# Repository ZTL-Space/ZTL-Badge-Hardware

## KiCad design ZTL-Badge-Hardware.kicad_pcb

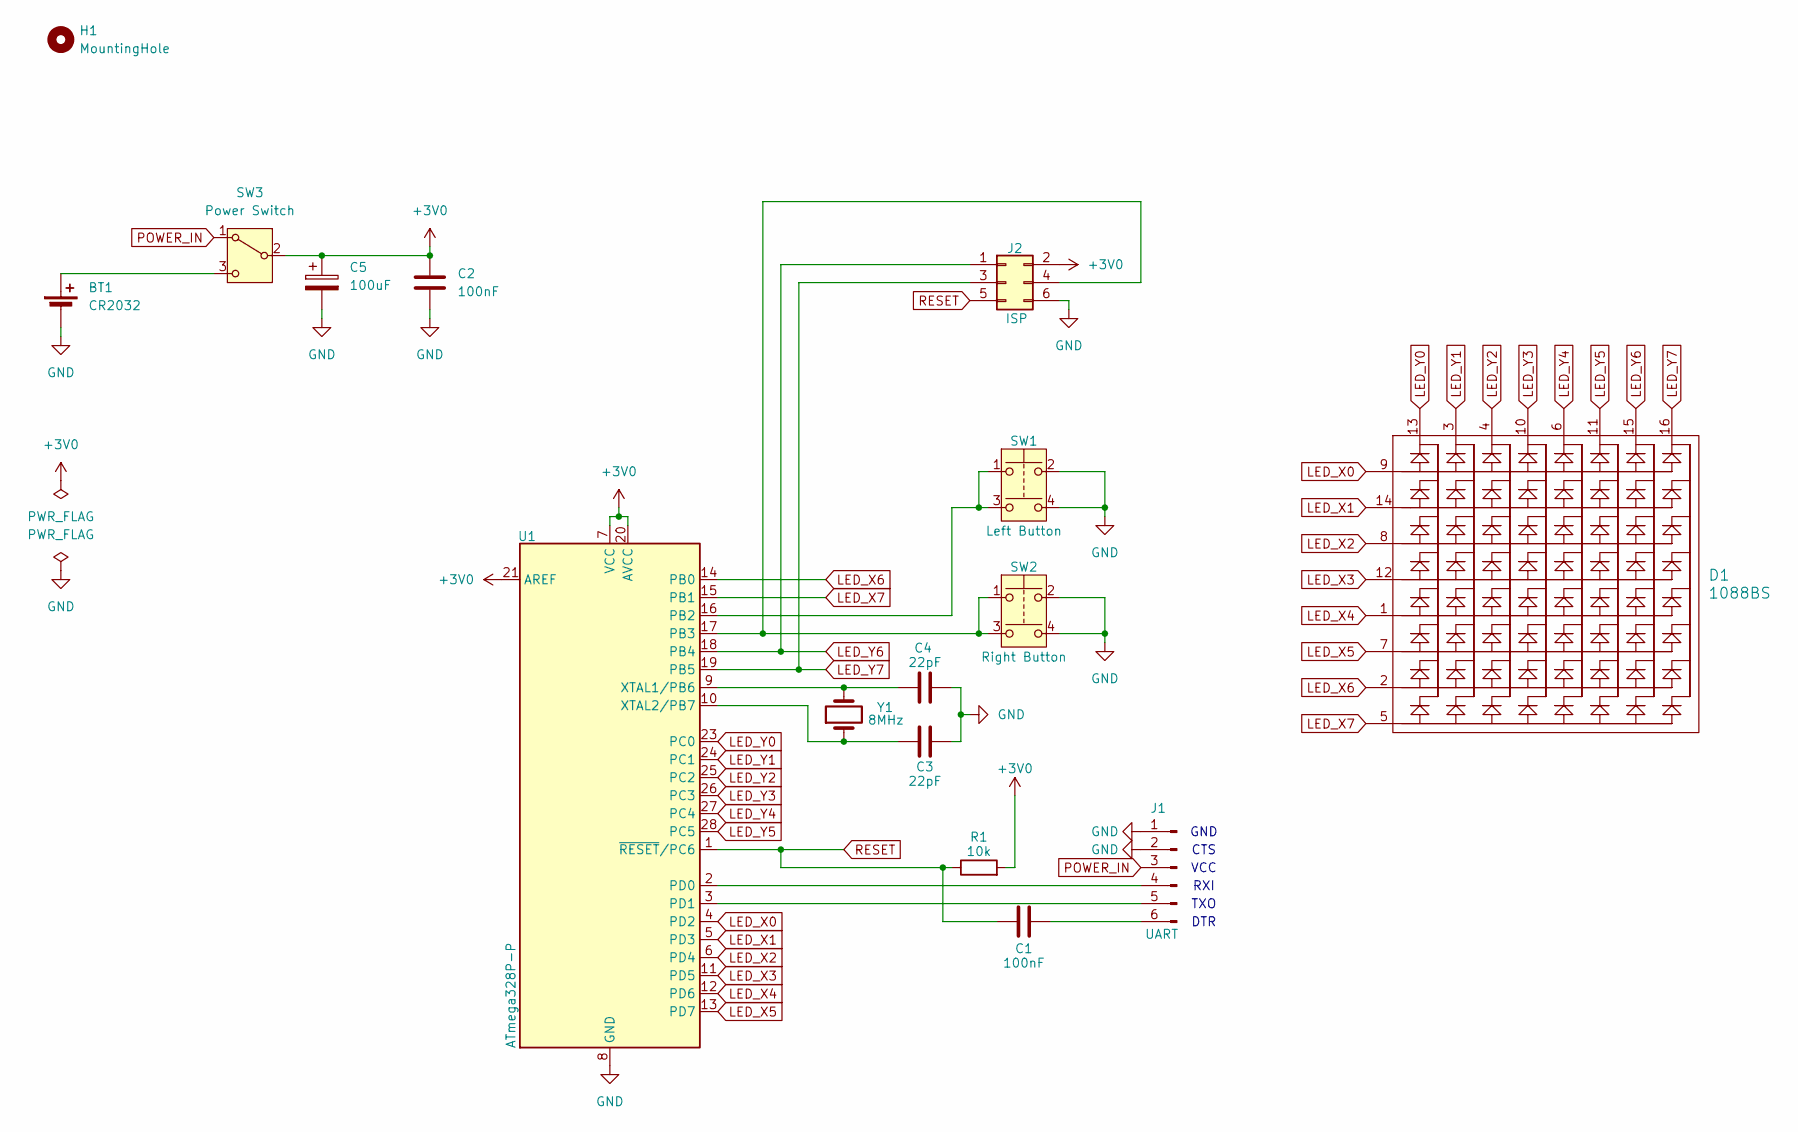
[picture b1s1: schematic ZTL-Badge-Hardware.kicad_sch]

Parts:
BT1: CR2032; Knopfzellenclip_20mm
C1, C2: 100nF; C_Disc_D3.8mm_W2.6mm_P2.50mm
C3, C4: 22pF; C_Disc_D3.8mm_W2.6mm_P2.50mm
C5: 100uF; CP_Radial_D5.0mm_P2.50mm
D1: 1088BS
H1: MountingHole; MountingHole_5.3mm_M5_DIN965_Pad
J1: UART; PinHeader_1x06_P2.54mm_Horizontal
J2: ISP; PinHeader_2x03_P2.54mm_Vertical
R1: 10k; R_Axial_DIN0207_L6.3mm_D2.5mm_P7.62mm_Horizontal
SW1: Left Button; Kurzhubtaster
SW2: Right Button; Kurzhubtaster
SW3: Power Switch; ESP101
U1: ATmega328P-P; DIP-28_W7.62mm
Y1: 8MHz; Crystal_HC49-4H_Vertical

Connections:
+3V0: C2.1, C5.1, J2.2, R1.2, SW3.2 (B), U1.7 (VCC), U1.20 (AVCC), U1.21 (AREF)
GND: BT1.2 (-), C2.2, C3.2, C4.2, C5.2, J1.1, J1.2, J2.6, SW1.2, SW1.4, SW2.2, SW2.4, U1.8 (GND), U1.22 (GND)
LED_X0: D1.9, U1.4 (PD2)
LED_X1: D1.14, U1.5 (PD3)
LED_X2: D1.8, U1.6 (PD4)
LED_X3: D1.12, U1.11 (PD5)
LED_X4: D1.1, U1.12 (PD6)
LED_X5: D1.7, U1.13 (PD7)
LED_X6: D1.2, U1.14 (PB0)
LED_X7: D1.5, U1.15 (PB1)
LED_Y0: D1.13, U1.23 (PC0)
LED_Y1: D1.3, U1.24 (PC1)
LED_Y2: D1.4, U1.25 (PC2)
LED_Y3: D1.10, U1.26 (PC3)
LED_Y4: D1.6, U1.27 (PC4)
LED_Y5: D1.11, U1.28 (PC5)
LED_Y6: D1.15, J2.1, U1.18 (PB4)
LED_Y7: D1.16, J2.3, U1.19 (PB5)
unnamed: BT1.1 (+), SW3.3 (C)
unnamed: J1.4, U1.2 (PD0)
unnamed: J1.5, U1.3 (PD1)
unnamed: C1.2, J1.6
unnamed: J2.4, SW2.1, SW2.3, U1.17 (PB3)
unnamed: SW1.1, SW1.3, U1.16 (PB2)
unnamed: C4.1, U1.9 (XTAL1/PB6), Y1.2
unnamed: C3.1, U1.10 (XTAL2/PB7), Y1.1
POWER_IN: J1.3, SW3.1 (A)
RESET: C1.1, J2.5, R1.1, U1.1 (~RESET/PC6)

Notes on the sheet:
DTR
CTS
TXO
RXI
VCC
GND

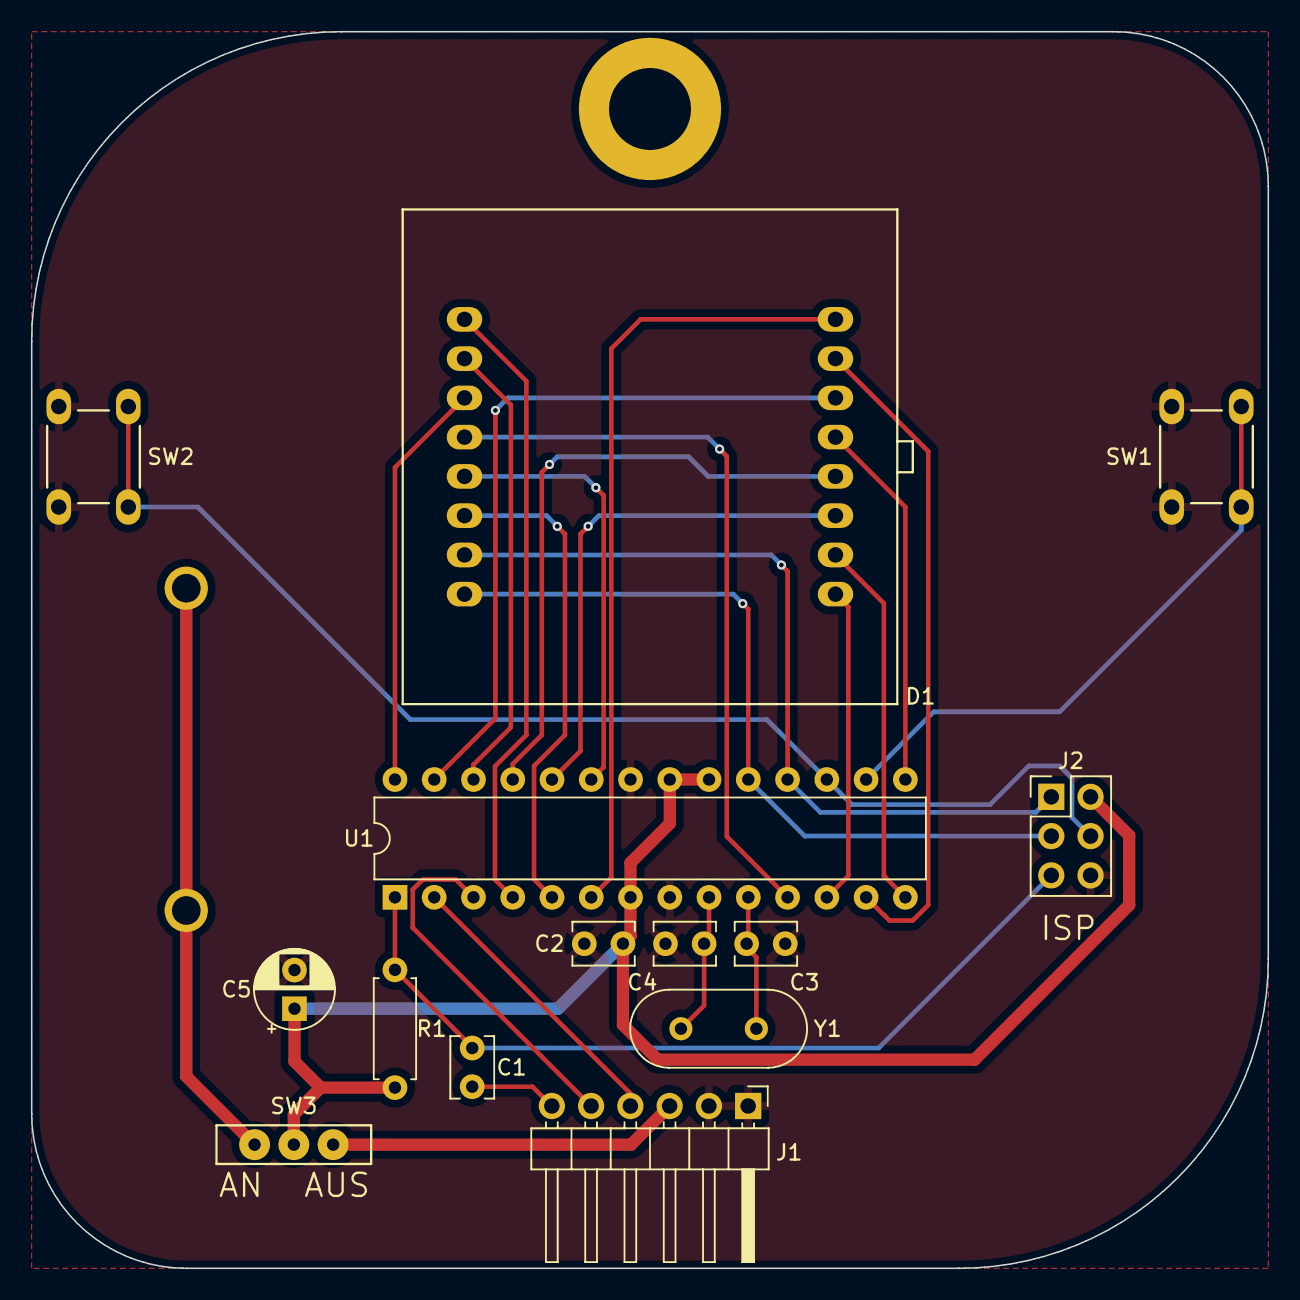
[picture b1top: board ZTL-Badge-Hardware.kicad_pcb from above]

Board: 2 copper layers, 80.0 x 80.0 mm, 16 parts (1 on the bottom side), 28 nets.

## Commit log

2024-03-03 initial commit with schematic
2024-07-27 first layout
